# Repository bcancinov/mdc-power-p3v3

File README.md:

# mdc-power-p3v3
Modular Detector Controller Power 3.3V DC-DC Mezzanine Module

## Overview
12V input to 3.3V output DC-DC module, 8A nominal output, used as one of the `mdc-power-*` bias rails.
Designed for 2 MHz sync operation.
Mezzanine module.

## Power Stage
- Controller: `LT8627SP` (`U1`)
  - Silent Switcher 3 synchronous step-down regulator.
  - Ultralow EMI emissions and high efficiency at high switching frequency.
  - Constant-frequency current-mode control.
  - External sync capability.
- Inductor: `L1` = `1uH`
  - Uses the XGL5030 shielded power inductor family (see `docs/xgl5030.pdf`).
  - Shielded construction to reduce radiated EMI and coupling into sensitive nodes.
  - Very low DCR family to reduce copper loss and improve efficiency.
  - Low AC loss construction optimized for high-frequency switching.

## Files
- Schematic: `power_p3v3.pdf`
- Simulation: `sim/` (LTspice and LTpowerCAD files used for loop and transient checks)

## Board Dimensions
- 44.8 mm x 41.5 mm

## Board Stackup
- 4-layer PCB

## CAD
- Designed using KiCad 9.

## Interface
- Control pins: `EN` (enable) and `PG` / `~PGOOD` (power good).
- Connector: `LSHM-140-04.0-L-DV-A-N-K-TR` (Samtec LSHM series) mezzanine for power and control signals.
  - Common pinout is shared across the 16V, -16V, 6V, and 3.3V variants.
  - Unused output rails are tied to GND on the specific module variant.

## Images
Layout:

3D view:

## License

This hardware design is licensed under the **Creative Commons Attribution-NonCommercial-ShareAlike 4.0 International License** (CC BY-NC-SA 4.0).

You are free to download, modify, and build upon this design for your own research or personal use, provided you give appropriate credit and share your modifications under the exact same license. **Commercial manufacturing or use of these designs is strictly prohibited without explicit permission.**

To view a copy of this license, visit [http://creativecommons.org/licenses/by-nc-sa/4.0/](http://creativecommons.org/licenses/by-nc-sa/4.0/) or see the `LICENSE` file in this repository.

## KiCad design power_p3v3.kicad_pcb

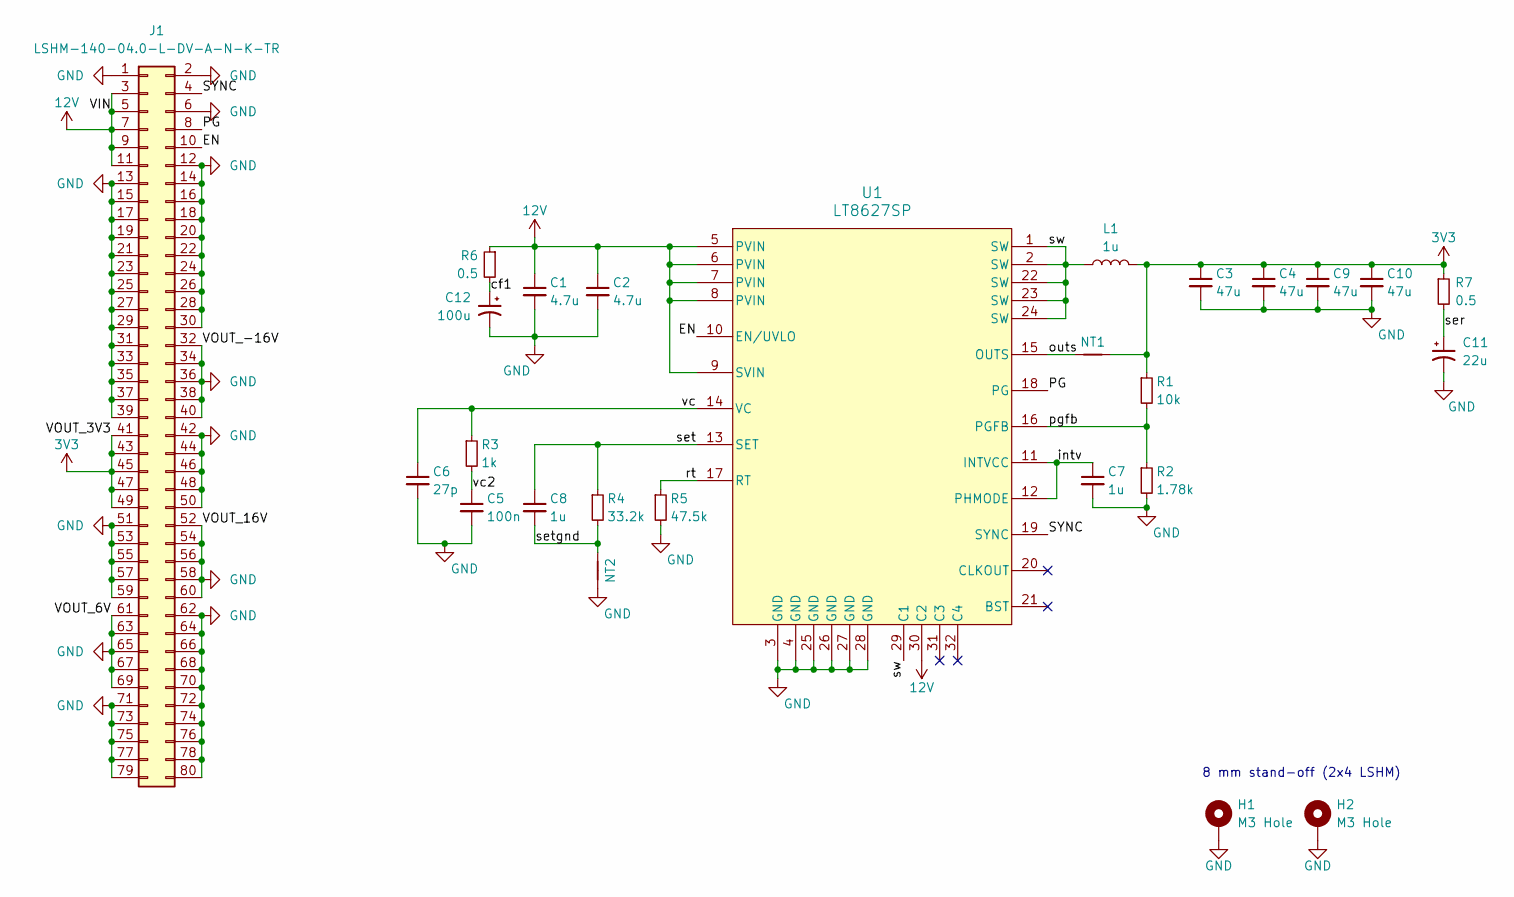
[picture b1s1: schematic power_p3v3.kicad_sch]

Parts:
C1, C2: 4.7u; C_1210_3225Metric; MPN GCM32ER71H475KA55K
C3, C4, C9, C10: 47u; C_1210_3225Metric; MPN TMK325ABJ476MM-P
C5: 100n; C_1206_3216Metric; MPN GCM31C5C1H104FA16L
C6: 27p; C_0603_1608Metric; MPN GCM1885C2A270FA16D
C7, C8: 1u; C_0805_2012Metric; MPN GCM21BR71H105KA03L
C11: 22u; CP_EIA-7343-20_Kemet-V; MPN T521V226M025ATE040
C12: 100u; T521X; MPN T521X107M025ATE060
H1, H2: M3 Hole; MountingHole_3.2mm_M3_Pad_Via
J1: LSHM-140-04.0-L-DV-A-N-K-TR; SAMTEC_LSHM-140-04.0-L-DV-A-N-K-TR; MPN LSHM-140-04.0-L-DV-A-N-K-TR
L1: 1u; XGL5030; MPN XGL5030-102MEC
NT1, NT2: NetTie_2; NetTie-2_SMD_Pad0.5mm
R1: 10k; R_0603_1608Metric; MPN CRCW060310K0FKEA
R2: 1.78k; R_0603_1608Metric; MPN CRCW06031K78FKEA
R3: 1k; R_0603_1608Metric; MPN CRCW06031K00FKEA
R4: 33.2k; R_0603_1608Metric; MPN ERA-3AEB333V
R5: 47.5k; R_0603_1608Metric; MPN CRCW060347K5FKEA
R6, R7: 0.5; R_0603_1608Metric; MPN RCWE0603R500FKEA
U1: LT8627SP; QFN-24_EP_4x4_Pitch0.5mm; MPN LT8627SPJV#TRPBF

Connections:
3V3: C3.1, C4.1, C9.1, C10.1, J1.41, J1.43, J1.45, J1.47, J1.49, L1.2, NT1.2, R1.1, R7.1
12V: C1.1, C2.1, J1.3, J1.5, J1.7, J1.9, J1.11, R6.1, U1.5 (PVIN), U1.6 (PVIN), U1.7 (PVIN), U1.8 (PVIN), U1.9 (SVIN), U1.30 (C2)
/EN: J1.10, U1.10 (EN/UVLO)
/PG: J1.8, U1.18 (PG)
/SYNC: J1.4, U1.19 (SYNC)
/cf1: C12.1, R6.2
/intv: C7.1, U1.11 (INTVCC), U1.12 (PHMODE)
/outs: NT1.1, U1.15 (OUTS)
/pgfb: R1.2, R2.1, U1.16 (PGFB)
/rt: R5.1, U1.17 (RT)
/ser: C11.1, R7.2
/set: C8.1, R4.1, U1.13 (SET)
/setgnd: C8.2, NT2.1, R4.2
/sw: L1.1, U1.1 (SW), U1.2 (SW), U1.22 (SW), U1.23 (SW), U1.24 (SW), U1.29 (C1)
/vc: C6.1, R3.1, U1.14 (VC)
/vc2: C5.1, R3.2
GND: C1.2, C2.2, C3.2, C4.2, C5.2, C6.2, C7.2, C9.2, C10.2, C11.2, C12.2, H1.1, H2.1, J1.1, J1.2, J1.6, J1.12, J1.13, J1.14, J1.15, J1.16, J1.17, J1.18, J1.19, J1.20, J1.21, J1.22, J1.23, J1.24, J1.25, J1.26, J1.27, J1.28, J1.29, J1.30, J1.31, J1.32, J1.33, J1.34, J1.35, J1.36, J1.37, J1.38, J1.39, J1.40, J1.42, J1.44, J1.46, J1.48, J1.50, J1.51, J1.52, J1.53, J1.54, J1.55, J1.56, J1.57, J1.58, J1.59, J1.60, J1.61, J1.62, J1.63, J1.64, J1.65, J1.66, J1.67, J1.68, J1.69, J1.70, J1.71, J1.72, J1.73, J1.74, J1.75, J1.76, J1.77, J1.78, J1.79, J1.80, NT2.2, R2.2, R5.2, U1.3 (GND), U1.4 (GND), U1.25 (GND), U1.26 (GND), U1.27 (GND), U1.28 (GND)

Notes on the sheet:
8 mm stand-off (2x4 LSHM)

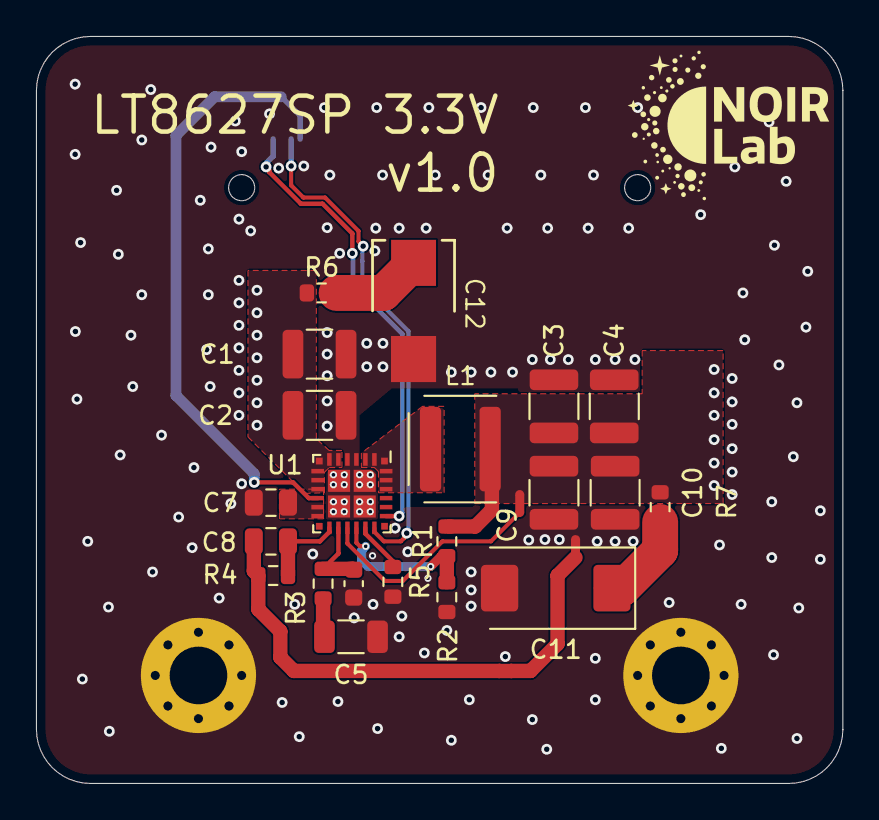
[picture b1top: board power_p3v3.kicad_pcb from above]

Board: 4 copper layers, 44.8 x 41.5 mm, 26 parts (1 on the bottom side), 17 nets.

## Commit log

2026-02-06 Add BOM
2026-02-06 update readme and docs
2026-02-17 Add Ferrite Beads
2026-03-18 update set resistor to thin film
2026-03-27 add license
